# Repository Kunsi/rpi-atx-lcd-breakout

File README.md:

# RPi-ATX-LCD-Breakout

This board allows you to connect an ATX power supply and a HD44780-compatible LCD
screen to your Raspberry Pi (or others with compatible GPIO layout).

While it does have a 40pin GPIO connector, it will also work with older 
26-pin variants of the Pi.

The board was created to provide a convenient interface for two
[Octoprint](http://octoprint.org/) plugins:
[PSUControl](https://github.com/kantlivelong/OctoPrint-PSUControl) and
[LCD-HD44780](https://github.com/Kunsi/Octoprint-LCD-HD44780) (See links on
bottom of this page).

The board itself offers a variety of features:
* Powering the Pi using +5VSB (standby power)
* Switching the PSU on and off using GPIO pin 12
  
  The GPIO pin can be connected to PS_ON directly, or via a transistor. This is
  choosable using the three-pin jumper switch.

   -Use pins 2 & 3 on jumper J1 to select PS_ON in direct connection mode, 
    if your psu pulls up to 3.3V or less.  
   -Use pins 1 & 1 on jumper J1 to select the transistor function if your 
    psu does pull up the PS_ON line to more than 3.3V. 

  Alternatively, the PSU can be forced to be on, by using the 2-pin PS_ON
  jumper, J2. You can wire a switch to these pins to turn on the powersupply
  acting like a manual overide. 

* Providing a "is the PSU on"-detection by wiring GPIO pin 11 to the 3v3 rail
  of the PSU
* Connecting a character LCD to the Pi
  
  LCD is wired as follows:
  <dl>
    <dt>Register Select</dt>
    <dd>15</dd>

    <dt>Enable</dt>
    <dd>16</dd>

    <dt>Data 4</dt>
    <dd>21</dd>

    <dt>Data 5</dt>
    <dd>22</dd>

    <dt>Data 6</dt>
    <dd>23</dd>

    <dt>Data 7</dt>
    <dd>24</dd>
  </dl>

  Data 0-3 pins are not connected. Read/Write select has been wired to GND, so
  it's not possible to read data from the LCD screen. Contrast pin is
  connected to a potentiometer.
* Allow connecting of two fans, one 5V, one 12V
* Providing screw terminals for GND, +12V, +5VSB and +5V
* Providing a USB outlet powered by +5VSB

Note: All pin numbers use BOARD numbering.

## Cost
Prices are in Euro, and are based on my prototype production cost

Item            | Count    | Price | Link
----------------|---------:|------:|---
PCB             | 1        | 1.70  | [PCBway](https://www.pcbway.com/) got me 10 boards for 17$
Fan connector   | 2        | 0.42  | <https://www.reichelt.de/?ARTICLE=185658>
Pin header      | 3+2 wide | 0.09  | <https://www.reichelt.de/?ARTICLE=119891>
Potentiometer   | 1        | 0.38  | <https://www.reichelt.de/?ARTICLE=14951>
LCD connector   | 1        | 0.52  | <https://www.reichelt.de/?ARTICLE=175351>
Screw terminals | 2        | 0.42  | <https://www.reichelt.de/?ARTICLE=170222>
Jumper          | 1        | 0.03  | <https://www.reichelt.de/?ARTICLE=119944>
USB connector   | 1        | 0.20  | <https://www.reichelt.de/?ARTICLE=22184>
Transistor      | 1        | 0.09  | <https://www.reichelt.de/?ARTICLE=1999>
Resistors       | 1+1+1    | 0.30  | <https://www.reichelt.de/?ARTICLE=1381><br> <https://www.reichelt.de/?ARTICLE=1315><br> <https://www.reichelt.de/?ARTICLE=1338>
GPIO connector  | 1        | 0.11  | [https://de.aliexpress.com/…/32454935478.html](https://de.aliexpress.com/item/100pcs-lot-2-54mm-Double-Row-Female-12P-Straight-Header-Pitch-Socket-Strip-2X20-Pin/32454935478.html)
ATX connector   | 1        | 0.43  | <http://www.mouser.de/ProductDetail/TE-Connectivity/1-1775099-3/>

## Links
* [Octoprint](http://octoprint.org/)
* [OctoPrint-PSUControl](https://github.com/kantlivelong/OctoPrint-PSUControl) by kantlivelong
* [Octoprint-LCD-HD44780](https://github.com/Kunsi/Octoprint-LCD-HD44780) by Kunsi

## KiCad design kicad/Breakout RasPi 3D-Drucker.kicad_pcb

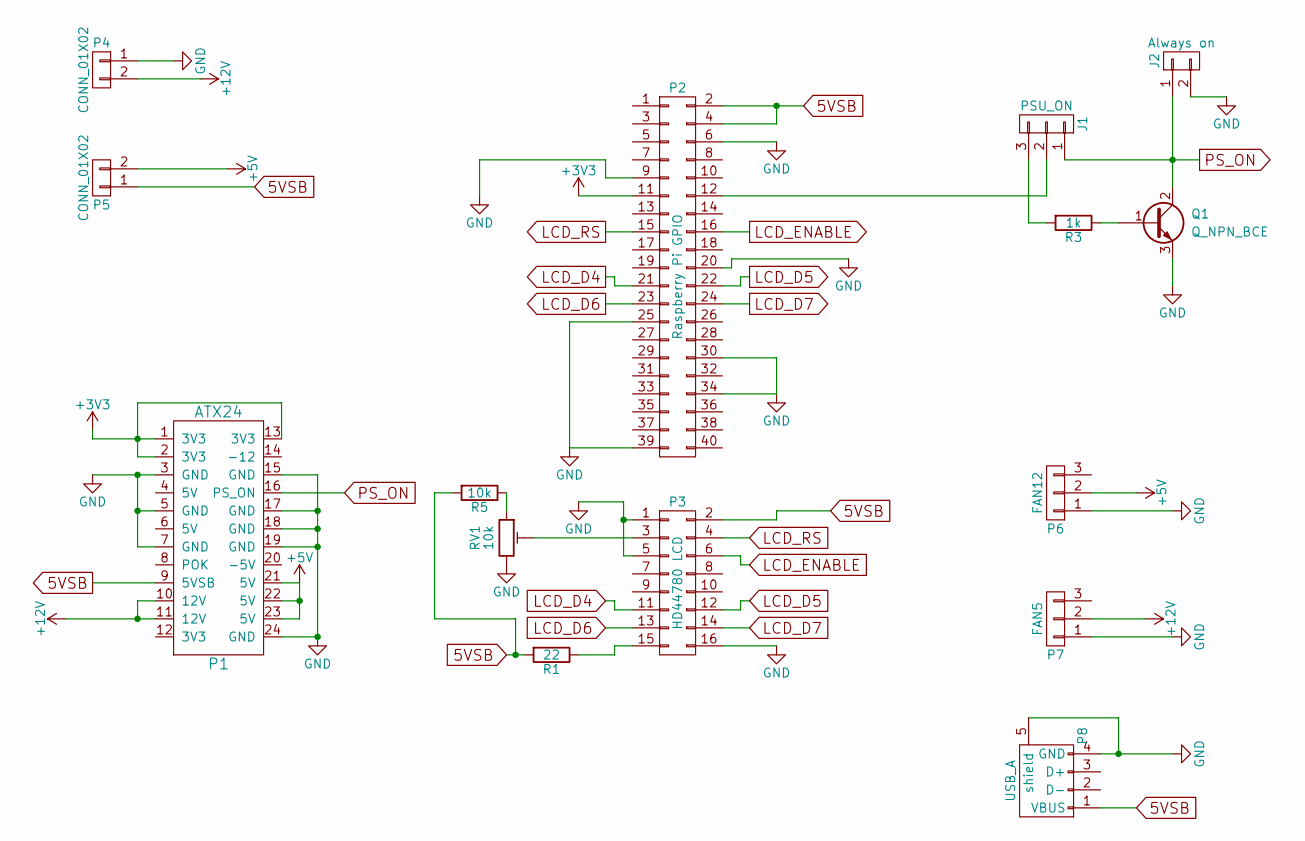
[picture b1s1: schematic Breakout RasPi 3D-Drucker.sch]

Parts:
J1: PSU_ON; Pin_Header_Straight_1x03
J2: Always on; Pin_Header_Straight_1x02
P1: ATX24
P2: Raspberry Pi GPIO; Socket_Strip_Straight_2x20
P3: HD44780 LCD; IDC_Header_Straight_16pins
P4, P5: CONN_01X02; RND_205-00001
P6: FAN12; Molex_KK-6410-03_03x2.54mm_Straight
P7: FAN5; Molex_KK-6410-03_03x2.54mm_Straight
P8: USB_A
Q1: Q_NPN_BCE; TO-92_Inline_Narrow_Oval
R1: 22; Resistor_Horizontal_RM7mm
R3: 1k; Resistor_Horizontal_RM7mm
R5: 10k; Resistor_Horizontal_RM7mm
RV1: 10k; Potentiometer_Trimmer-Piher_PT15-V12-5_horizontal_revers

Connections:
5VSB: P1.9 (5VSB), P2.2, P2.4, P3.2, P5.1, P8.1 (VBUS), R1.2, R5.2
+3V3: P1.1 (3V3), P1.2 (3V3), P1.13 (3V3), P2.11
+5V: P1.21 (5V), P1.22 (5V), P1.23 (5V), P5.2, P6.2
+12V: P1.10 (12V), P1.11 (12V), P4.2, P7.2
GND: J2.2, P1.3 (GND), P1.5 (GND), P1.7 (GND), P1.15 (GND), P1.17 (GND), P1.18 (GND), P1.19 (GND), P1.24 (GND), P2.6, P2.9, P2.20, P2.25, P2.30, P2.34, P2.39, P3.1, P3.5, P3.16, P4.1, P6.1, P7.1, P8.4 (GND), P8.5 (shield), Q1.3 (E), RV1.3
LCD_D4: P2.21, P3.11
LCD_D5: P2.22, P3.12
LCD_D6: P2.23, P3.13
LCD_D7: P2.24, P3.14
LCD_ENABLE: P2.16, P3.6
LCD_RS: P2.15, P3.4
unnamed: J1.2, P2.12
unnamed: J1.3, R3.2
unnamed: P3.3, RV1.2
unnamed: P3.15, R1.1
unnamed: Q1.1 (B), R3.1
unnamed: R5.1, RV1.1
PS_ON: J1.1, J2.1, P1.16 (PS_ON), Q1.2 (C)

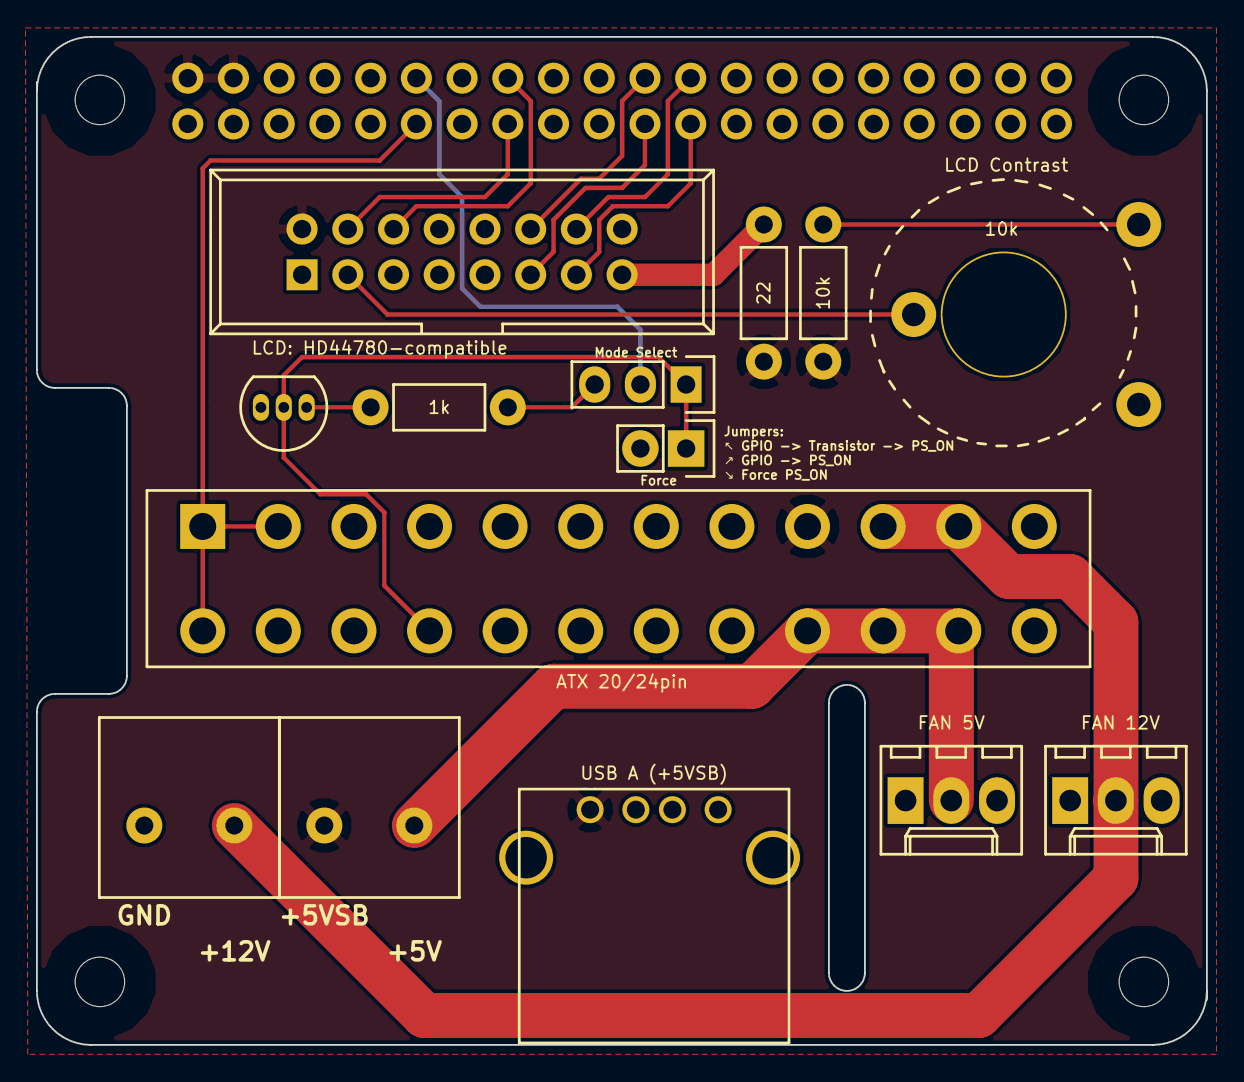
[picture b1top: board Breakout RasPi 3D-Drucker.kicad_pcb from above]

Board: 2 copper layers, 65.0 x 56.0 mm, 15 parts (1 on the bottom side), 18 nets.

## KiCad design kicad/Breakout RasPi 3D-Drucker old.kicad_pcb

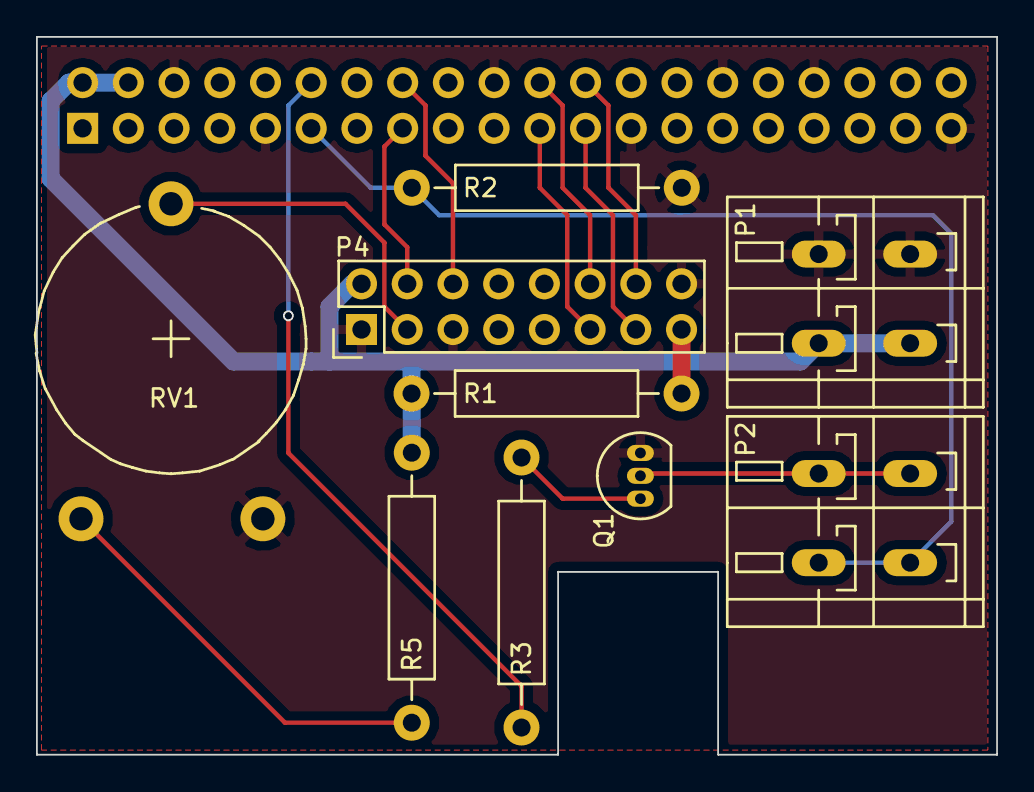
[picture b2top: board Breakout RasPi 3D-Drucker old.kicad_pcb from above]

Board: 2 copper layers, 53.3 x 39.9 mm, 10 parts (1 on the bottom side), 15 nets.

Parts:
P1: Power; TerminalBlock_WAGO-236_2Stift_RM5mm_2pol
P2: PSU_Control; TerminalBlock_WAGO-236_2Stift_RM5mm_2pol
P3: Raspberry Pi GPIO; Socket_Strip_Straight_2x20
P4: HD44780 LCD; Pin_Header_Straight_2x08
Q1: Q_NPN_BCE; TO-92_Inline_Narrow_Oval
R1: 22; Resistor_Horizontal_RM15mm
R2, R5: 10k; Resistor_Horizontal_RM15mm
R3: 1k; Resistor_Horizontal_RM15mm
RV1: 10k; Potentiometer_Trimmer-Piher_PT15-V17-5_horizontal

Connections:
+3V3: P2.1, P3.11, R2.1
+5V: P1.1, P3.2, P3.4, P4.2, R1.2, R5.2
GND: P1.2, P3.6, P3.9, P3.20, P3.25, P3.30, P3.34, P3.39, P4.1, P4.5, P4.16, Q1.3, R2.2, RV1.3
LCD_D4: P3.21, P4.11
LCD_D5: P3.22, P4.12
LCD_D6: P3.23, P4.13
LCD_D7: P3.24, P4.14
LCD_ENABLE: P3.16, P4.6
LCD_RS: P3.15, P4.4
unnamed: P3.12, R3.2
unnamed: P4.3, RV1.2
unnamed: P4.15, R1.1
unnamed: Q1.1, R3.1
unnamed: R5.1, RV1.1
PS_ON: P2.2, Q1.2

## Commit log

2017-06-12 Add cost of PCB and parts
2017-06-12 README: fix formatting
2017-06-14 README: Add Info about pin 11 (3V3 in)
2017-07-24 README: fix typo
    HD44780-comptible -> HD44780-compatible
